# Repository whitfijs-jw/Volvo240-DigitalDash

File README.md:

# DigitalDash

Volvo 240 Digital Dash Project.  Designed to use existing dash connectors (circular connectors w/ 2mm pins, vehicle speed sensor (VSS) connector, and various spade connectors) to
minimize extra wiring effort and installation of superfluous sensors.

## Features
### Plug and play with stock sensors and dash connectors
One of the main goals of the project was to use the existing Volvo 240 connectors. The only additional connectors and wiring needed are for sensors that weren't available on the stock main dash (oil pressure, oil temperature, vacuum/boost pressure, etc). Dash lights (low oil pressure, battery voltage, parking brake,high beams, etc) are functional as well as turn indicators. Fuel level and coolant temperature are functional.
The hardware supports the addition of common accessory sensors such as oil pressure, oil temperature, manifold absolute pressure, and ambient temperature.

### Multiple dash styles
Different Volvo dash styles can be displayed:
#### 240 w/ Tach

#### 240 w/ Clock

#### R-Sport Style

#### P1800 Style

#### 850R

#### 740/940 Style

#### 544/140 Linear Style

#### Early 240 Style

#### 140 Rallye Style

#### 240 Style Custom Layouts

### Accessory Gauges
The raspberry pi 4 supports 2 HDMI outputs so a second screen can be added where normal 52mm accessory gauges would have been placed:

Touch screen controls on this screen can be used to changed between dash layouts and also to reset trip odometers.  The style of the accessory gauges reflects the style of the main dash layout.

## Project Structure:
### /QtDash

This directory contains the hardware and software components that makeup the dash. There are also various visual/graphical assets that are used in the dash app.

#### /QtDash/VolvoDigitalDashModels

This directory contains the Qt app and related unit tests.  It is advised to use [QtCreator](https://www.qt.io/product/development-tools) to edit and compile the app. Using QtCreator to `QtDash/VolvoDigitalDashModels/subdirs.pro` will load both the app and the unit tests. The app is written using C/C++ for interfacing with the various sensors and QML for the UI.

#### /QtDash/Hardware

This directory contains the hardware that has been designed for this project.  Most of the PCBs have been designed using Eagle 7.7 as this is what I am most familiar with. The future of Eagle is questionable as an open source/free tool, so Kicad 6 will be used more and more as I become more familiar with it.

##### /QtDash/Hardware/DashHat

This directory contains the schematics and board files for the PCB that directly interfaces with the Raspberry Pi 40 pin header.  The board is split up into a low voltage (3.3/5V) that is powered from the Pi header and a high voltage (car battery voltage 8-16V) that is powered from the 240 ignition switch via the VSS connector.  The high voltage side is optically isolated from the low voltage side using optoislators.

##### /QtDash/Hardware/Cold Start Power Supply

This directory contains the schematics and board files for the cold start tolerant power supply design based around the LM3488. The input range is ~3V-24V and the output is ~5V rated at 3A.  During bench testing the input power needs to be above 5V when first powering up, and then could drop to ~3V while still continuously powering the Pi. This is a little overkill as the battery voltage during cranking only momentarily drops to 3V-4V before recovering very quickly to >10V.

##### /QtDash/Hardware/Screen Mounting

This directory contains the `.stl` files for mounting the HSD123KPW2-D10 12.3" TFT LCD using the stock 240 dash mounting holes.  These mounts will put the screen flush with the surrounding dash. The mounts and all other 3D modeling/CAD has been done using [Onshape](https://cad.onshape.com/documents/a41976d465f773bfdcbe5a50/w/2aee2fa256d8f08e0c531410/e/f563da56c6a88e94f86205e9). Included in the public OnShape document are models of the main PCB, HSD123KPW2-D10 LCD, screen mounts, etc.

##### /QtDash/Hardware/Simulation

This directory contains SPICE simulations of various circuits used in the dash. This is more of a scratchpad than it is a serious attempt at accurate real-life simulations.

##### /QtDash/Hardware/TachAdapter

This directory contains the schematics and board files for the tach signal adapter.  This board takes the high voltage pulses (>30V on my 88 245) and converts them to a square wave that can be used by the dash software to calculate RPM. The high voltage pulses are optically isolated from the dash/pi side to prevent any unwanted noise or damage to the pi or other hardware.

##### /QtDash/Hardware/VSS Adapter

This directory contains the schematics and board files for the VSS signal adapter. This board is based on the MAX9924 VR signal conditioning IC and takes the VR signal from the stock Volvo differential cover sensor and converts it into a square wave to be used by the dash software to calculated speed.

### /buildroot

This directory contains Buildroot, a tool used to generate a custom embedded Linux system that runs on the Pi. Buildroot allows us to generate a stripped down Linux system that has just enough to get the dash running.  This is the directory where you'll need to be to start linux image builds.

Below are relevant directories for this project within the buildroot directory structure:

#### /buildroot/board/volvodash

This directory contains the rootfs overlay for the dash as well as the custom scripts and configurations used whilst building the dash linux image. 

#### /buildroot/configs

This directory contains the configuration files for various boards. The relevant files for this project are `volvodash_defconfig` and `volvodash_rpi4_defconfig`.

#### /buildroot/output/images

This directory contains the outputs of the buildroot compilation process. After buildroot is done compiling the custom linux image, compiling the specified target packages, and constructing the target rootfs and bootfs, an image that can be flashed on to an SD card is placed here.  `sdcard.img` can then be flashed on to an SD card to be used on a pi.  As a part of the compilation/building the Qt Dash app should be compiled and placed within this image.  For more detailed information see *Setting Up Buildroot* below.

## Project components:
- Raspberry Pi 3 or Raspberry Pi 4/400
- 12.3" bar TFT LCD
- Qt Quick w/ EGLFS project to display renders of gauges
- Buildroot linux to cut down on footprint and boot time
- i2c/spi adc interface for reading temp, fuel, speed, etc sensors
- i2c IO expander for warning lights
- Raspberry Pi daughter board to read various sensors.
- DC/DC power supply for screen, pi and sensor supplies, if necessary
- Cheap USB GPS for speedometer and heading (leaving the original speedo behind the dash? Not planning on implementing a validated odometer)

## Current parts (mainly driven by availability):
- HSD123KPW2-D10 12.3" TFT 1920x720 LCD Display w/ HDMI conversion board and custom mounts
- MCP3208 for ADC inputs
- MCP23017SS for dash warning lights and left/right blinkers
- ILQ1 for isolated I/O inputs (3 for 12 inputs) add one more to completely fill the MCP23017
- IL300 for 12V to 3.3V for isolated analog signals (rheostat and battery voltage)
- lM358D for driving IL300 12V isolated analog inputs
- LMV324 & TVS912D for 5V to 3.3V analog sensor inputs
- VK-162 USB GPS module -- needs to be manually configured with u-blox u-center to get 10Hz update rate.
- (optional and separate) LM3488 switching power supply to maintain 5.1V out from 3V-24V input
- (optional) MAX9924 VSS conditioning circuit
- (separate) optocoupler tach pulse input.

## Accessory Screen Parts (optional)
- Adafruit TFP401 HDMI/DVI Decoder to 40-Pin TTL Breakout - With Touch
- BuyDisplay.com 5" IPS 800x480 LCD Screen TFT w/ touch module ER-TFT050-6-5781-4859
- extended 40-pin flat cable
- USB cable for touch screen interface

## Setting up buildroot

Buildroot will build the custom linux image.  The image being build is based on the raspberry-piX 32-bit images provided from the buildroot project.  Right now there is only support for raspberry pi 3 and pi 4/400.  Things are still a bit of a mess here and depending on your flavor of Linux you might have to setup your system a little differently than others.  You can find a lot of good information here on host packages that are absolutely necessary: [Buildroot System Requirements](https://buildroot.org/downloads/manual/manual.html#requirement)

Detailed instructions for setting up a virtual machine and the build environment are found [here](SetupBuildEnv.md)

## Remote Access

1. SSH (ethernet)

After boot the pi will be configured with a static ip address of 192.168.42.2.
Assuming you're running a version of linux that has network-manager you can run some variation of the following after connecting the pi to your computer with an ethernet cable:

`nmcli con add con-name dash-target type ethernet ifname <your-ethernet-interface> ip4 192.168.42.1/24`

`nmcli con up id dash-target`

You can find your ethernet interface by running:

`ip addr show`

You're looking for something like `enp2s0` or `eth0` depending on your flavor of linux.

After setting everything up you can test the connection using:

`ping 192.168.42.2` 

on the host machine and then run:

`ssh root@192.168.42.2` 

and enter the default credentials

## Dash Configuration

After linux is done booting and loading kernel modules, the init system will automatically start the Qt app stored in the /opt directory.  When the app is initializing it will load two configuration files from the /opt directory:

- config.ini
- config_gauges.ini
- config_odo.ini
- config_can.ini

These files are parsed using QSettings ([more info here](https://doc.qt.io/qt-5/qsettings.html)).

### Sensor input configuration (config.ini)

The sensor configuration file contains the configuration for the analog sensor inputs, dash light inputs, user inputs, tach inputs, vss inputs, the isolated 12V inputs, and backlight PWM control.

#### Sensor channels

Under the **[sensor_channel]** section the following inputs can be configured:

| Parameter | Description |
|---|---|
| *coolant_temp* | Stock Volvo coolant temperature sensor/sender. |
| *fuel_level* | Stock Volvo Fuel Level sender |
| *oil_pressure* | Oil Pressure sender |
| *oil_temp* | Oil temperature sender |
| *map_sensor* | MAP sensor sensor (GM 0-5V) |
| *ambient_temp* | Ambient Temperature sender (any NTC sensor can be used) |
| *dimmer_voltage* | Dimmer Rheostat output voltage |
| *fuse8_12v* | Volvo Fuse 8 to measure battery voltage |
| *reference* | A channel configured to measure the unregulated pi 5V supply to decrease measurment error.  If this is not used it is assumed that the supply is exactly 5V. You can alternatively measure your 5V power rail and provide that in the configurations below.|
| *v_supply* | Optional value to set the exact value of the 5V supply.  If left empty exactly 5.0V will be used |

The default configuration is as follows:
```
[sensor_channels]
coolant_temp=0
fuel_level=1
oil_pressure=2
oil_temp=3
map_sensor=5
ambient_temp=4
dimmer_voltage=6
fuse8_12v=7
reference=-1
v_supply=5.1
```

#### Dash Light Inputs

Under the **[dash_lights]** section the following inputs can be configured:

| Parameter | Description |
|---|---|
| *oil_pressure_sw* | Stock oil pressure switch |
| *od_lamp* | Overdrive lamp |
| *high_beam* | High beam indication |
| *brake_failure* | brake failure indication |
| *bulb_failure* | bulb failure indication |
| *charging* | Alternator D+/Battery charge failure indication |
| *blinker_left* | Left blinker indication |
| *blinker_right* | Right blinker indication |
| *od_lamp_auto* | auto trans OD lamp |
| *check_engine* | Check Engine indication |
| *parking_brake* | Parking Brake engagement indication |
| *conn_32_pin3* | Half moon connector pin 3 (ABS light in newer 240s) |

and one additional option:

- *active_low* -- Optoisolator outputs are open collector so this should be set to 1 unless changes to the hardware have been made

The default configuration is as follows:

```
[dash_lights]
active_low=1
oil_pressure_sw=0
od_lamp=1
high_beam=2
brake_failure=3
bulb_failure=7
charging=6
blinker_left=5
blinker_right=4
od_lamp_auto=8
check_engine=9
parking_brake=10
conn_32_pin3=11
```
#### User Input configuration

There are 4 user inputs in Rev C and greater hardware.  They are active low inputs on the otherwise unused pins on the MCP23017.

Under the **[user_inputs]** section the following inputs can be configured:

| Parameter | Description |
|---|---|
| *input_1* | User input 1 pin number |
| *input_2* | User input 2 pin number |
| *input_3* | User input 3 pin number |
| *input_4* | User input 4 pin number |
| *input_1_map* | User input 1 key mapping |
| *input_2_map* | User input 2 key mapping |
| *input_3_map* | User input 3 key mapping |
| *input_4_map* | User input 4 key mapping |

The default configuration is as follows:

```
[user_inputs]
input_1=12
input_2=13
input_3=14
input_4=15
input_1_map="Key_Left"
input_2_map="Key_A"
input_3_map="Key_B"
input_4_map="Key_Right"
```

Available key mappings are:
```
"Key_Left"
"Key_Right"
"Key_Up"
"Key_Down"
"Key_A"
"Key_B"
"Key_C"
"Key_D"
"Key_1"
"Key_2"
"Key_3"
"Key_4"
```

"Key_Left" and "Key_Right" are used to change dash layouts.  Other keys will be mapped to other functions in the future (resetting trip counters, for example).

#### MAP Sensor configuration

Designed for a GM style 0-5V output MAP sensor (1 bar, 2 bar, 3 bar). Under the **[map_sensor]** section the following parameters can be configured:

| Parameter | Description |
|---|---|
| *p_0v* | pressure when sensor output is 0V |
| *p_5v* | pressure when sensor output is 5V |
| *p_atm* | atmospheric pressure |
| *units* | pressure units used for above values.  "kPa", "psi" or "bar" should be used |

The default configuration is for a 3 bar GM style map sensor:

```
[map_sensor]
p_0v=3.6
p_5v=315
units="kPa"
```

#### Temperature Sensor (NTC) Configuration

An array of NTC sensor configurations. Calibration curves are calculated using the [Steinhart-Hart equation](https://en.wikipedia.org/wiki/Steinhart%E2%80%93Hart_equation). Under the **[temp_sensor]** the following parameters can be configured:

| Parameter | Description |
|---|---|
| *type* | Sensor type.  Options are "coolant", "oil", and "ambient" |
| *r_balance* | Resistance of the balance resistor. This can be calculated based on the high and low resistances expected during operation. |
| *t1_temp* 	|  Temperature at first calibration point |
| *t1_R* 		| Resistance at first calibration point |
| *t2_temp* 	| Temperature at second calibration point |
| *t2_R* 		| Resistance at second calibration point |
| *t3_temp* 	| Temperature at third calibration point |
| *t3_R* 		| Resistance at third valibration point |
| units | Temperature units used.  Options are "C", "K", "F" |

The default configuration is designed for an early type stock 240 coolant temp sensor, a VDO 325-905 Oil temperature sender, and a random ambient temp sensor for a BMW off Amazon.

```
[temp_sensor]
size=3
[temp_sensor/1]
type="coolant"
r_balance=470
t1_temp=60
t1_R=217
t2_temp=90
t2_R=87
t3_temp=100
t3_R=67
units="C"
[temp_sensor/2]
type="oil"
r_balance=150.0
t1_temp=19.5
t1_R=1325
t2_temp=100
t2_R=78.5
t3_temp=157
t3_R=40.5
units="C"
[temp_sensor/3]
type="ambient"
r_balance=6490
t1_temp=1.0
t1_R=15800
t2_temp=20
t2_R=6400
t3_temp=36
t3_R=3360
units="C"
```

#### Resistive Sensor Configuration

An array of resistive sensor configurations. Calibration values can be interpolated (not advised unless a lot of data points are available) or can be fitted with a polynomial of an arbitray order.  Usually a 2nd order polynomial is good enough.  The following parameters can be configured:

| Parameter | Description |
|---|---|
| *type* | Sensor type.  Options are "coolant", "oil", and "ambient" |
| *fit* | Type of fit. Options are "interpolate" or "polynomial, N" with N as the polynomial order.
| *r_balance* | Resistance of the balance resistor. This can be calculated based on the high and low resistances expected during operation. |
| *r* | Calibration resistance values.|
| *y* | Calibration y values |
| *units* | Units of calibration y values |
| *lag* | Lag factor (0-1).  Used to filter values with the difference equation: **y[n] = lag \* x[n] + (1 - lag) \* y[n-1]** Default value is 1.0. |
|*lag_decay*| Lag decay factor.  If set to a non-zero value the following equation will dictate the lag factor value used above: **lagStart=1-*lag*, lag[n] = lagStart \* (1 - *lag_decay*)^(n)** and saturates at the value set by *lag*. Large values will decay quickly, small values slowly.  Default value is 0.0.  |

The default configuration is designed for a VDO 360-028 Oil pressure sender and a 240-33Ohm Volvo 240 Fuel level sender.

```
[resistive_sensor]
size=2
[resistive_sensor/1]
type="oil_pressure"
fit=polynomial,2
r_balance=43.0
r=10.0,48.0,82.0,116.0,184.0
y=0.0,1.0,2.0,3.0,5.0
units="bar"
lag=1.0
[resistive_sensor/2]
type="fuel_level"
fit=polynomial,3
r_balance=91.0
r=240,196,153,125,103,87,67,45,33
y=0.0,12.5,25.0,37.5,50.0,62.5,75.0,87.5,100
units="%"
lag=0.2
```

#### Analog 12V inputs.

To measure signals that are inherently tied to battery voltage there are 2 linearized opto-isolated inputs.  The following parameters can be configured:

| Parameter | Description |
|---|---|
| *name* | Sensor name.  "voltmeter" is the only one currently used |
| *opto_r1* | Isolated side (R59 in schematic below) |
| *opto_r2* | Opto-isolator gain resistor R2 (R62 in schematic below) |
| *input_r1* | High side resistor of voltage divider for input into opto-isolator. (R71 in schematic below) |
| *input_r2* | Low side resistor of voltage divivider for input into opto-isolator. (R72 in schematic below) |
| *k3* | Opto-isolator K3 gain (defined by linearized opto-isolator used and will have to be measured) |
| *offset* | Offset to voltage calculation, the linearized opto-isolator usually has an offset that will need to be accounted for. |
| *x* | Linearized opto-isolator input voltage calibration measurements.  This is the high voltage side.  The more measurement points the better.   |
| *y* | Output voltage calibration measurements.  This is the low voltage side.  Ideally if there was zero offset and a K3 gain of 1.0 these should be x / 10.  This is unlikely to be the case given the binning of the IL300 and LOC11x series. |

##### How to determine K3 value (still need to test on car -- likely to change)
1. In the config.ini file, set *opto_r1*, *opto_r2*, *input_r1*, *input_r2*, and *k3* to 1.0.
2. In the config.ini file, set *offset* to 0.0.
3. Reboot the dash.
4. The output for the voltmeters will now be the real input to the ADC. Usually between 1V-2V for inputs from 8V to 16V.
5. With the car on but not running, measure the voltage at fuse 8.  This will be your first x value.  Take the output of the voltmeter (somewhere between 1V-2V).  This will be your first y value.
6. Start the car and repeat the above step.  These will be your second x and y values.
7. Enter the values determined above in the config.ini file.
8. Reset the *opto_r1*, *opto_r2*, *input_r1*, *input_r2* to their previous values.  You can leave *offset* and *k3* alone.  The software will use your calibration values to calculate the k3 gain and offset.
9. Reboot the dash and verify that the voltages with the car on and running match what you had measured before.

*Note on K3 gain calibration values:*
*Ideally, you would want way more than just 2 points to calibrate with.  If you have access to an adjustable power supply it is recommended to take 5+ measurements from 8V-16V.*

The default configuration is as follows:

```
[12v_analog]
size=2
[12v_analog/1]
name="voltmeter"
opto_r1=490000.0
opto_r2=100000.0
input_r1=100000.0
input_r2=100000.0
k3=1.1536
offset=.087985
x=8.25, 9.05, 9.87, 10.67, 11.52, 12.37, 13.30, 14.15, 14.96, 15.78, 16.78
y=1.05, 1.15, 1.25, 1.35, 1.45, 1.55, 1.65, 1.76, 1.85, 1.95, 2.05
[12v_analog/2]
name="rheostat"
opto_r1=490000.0
opto_r2=100000.0
input_r1=100000.0
input_r2=100000.0
k3=1.1536
offset=.087985
x=8.25, 9.05, 9.87, 10.67, 11.52, 12.37, 13.30, 14.15, 14.96, 15.78, 16.78
y=1.05, 1.15, 1.25, 1.35, 1.45, 1.55, 1.65, 1.76, 1.85, 1.95, 2.05
```

#### Tach Input Configuration

RPM is estimated by measuring the time difference between pulses from the negative terminal of the ignition coil.  The following parameters can be configured:

| Parameter | Description |
|---|---|
| *pulse_per_rot* | Number of tach pulses per rotation (number of cylinders / 2) |
| *max_rpm* | Maximum RPM to resolve.  This should be as low as possible. |
| *avg_num_samples* | Number of samples to average over to estimate RPM |

The default configuration is as follows:

```
[tach_input]
pulse_per_rot=2
max_rpm=9000
avg_num_samples=4
```

#### Vehicle speed sensor input

Designed to used the stock 240 diff cover VSS. The vehicle speed can be estimated using the number of pulses coming from the VSS sensor for every rotation of the rear diff. The following parameters can be configured:

| Parameter | Description |
|---|---|
| *pulse_per_rot* | Number of VSS pulses per rotation (12 for non-ABS and 48 for ABS equipped 240s) |
| *tire_diameter* | Tire diameter (can be used to calculate pulses per unit distance) |
| *diameter_units* | Tire diameter units: "inch", "centimeter", "millimeter", "foot", etc  |
| *pulse_per_unit_distance* | Number of pulses per units distance.   |
| *distance_units* | Distance units for pulses per unit distance:  "mile", "kilometer  |
| *max_speed* | max speed (distance_units / hour).  Keep as low as possible to avoid picking up noise as VSS pulses |

The default configuration is as follows:

```
[vss_input]
pulse_per_rot=12
tire_diameter=24.9
diameter_units="inch"
pulse_per_unit_distance=9720
distance_units="mile"
max_speed="185"
```

#### Backlight control configuration (optional and only somewhat functional)

The stock 240 dimming circuit (Pin 10 on the circular Volvo connector 31) can be used to dim the backlight of the LCD by injecting a PWM signal into the LCD control board. Back light control with the dimmer knob only works when the headlights or running lights are engaged.  Otherwise, the dimmer rheostat does not receive voltage.

The following parameters can be configured:

| Parameter | Description |
|---|---|
| *max_duty_cycle* | Maximimum duty cycle of backlight PWM signal (min_duty_cycle-1.0) |
| *min_duty_cycle* | Minimum duty cycle of backlight PWM signal (0-max_duty_cycle) |
| *lights_off_duty_cycle* | Default duty cycle to use when the headlights or running lights are off |
| *lights_on_duty_cycle* | Default duty cycle to use when headlights or running lights are on|
| *min_dimmer_ratio* | rheostat voltage as a percentage of battery voltage at dimmest setting |
| *max_dimmer_ratio* | rheostat voltage as a percentage of battery voltage at brightest setting |
| *use_dimmer* | flag to use/don't use dimmer |
| *active_low* | PWM signal active low flag |

The default configuration is as follows:

```
[backlight]
max_duty_cycle=1.0
min_duty_cycle=0.05
lights_off_duty_cycle=1.0
lights_on_duty_cycle=0.5
min_dimmer_ratio=0.82
max_dimmer_ratio=0.93
use_dimmer=0
active_low=1
```

### Gauge Configs (config_gauges.ini)
There are a few options in setting up the gauge units and high/low warning indications.  There settings are found within the file config_gauges.ini.  The app will parse this file and will set the various gauge units, min/max values, and high/low warnings.

#### Gauge Config Parameters
| Parameter | Description | Default Value |
|---|---|
|*units*| Gauge Display Units ||
|*low_alarm*| Value below which gauge will indicate a warning ||
|*high_alarm*| Value above which gauge will indicate a warning ||
|*alt_units_enable*| Enable alternate units|*false*|
|*alt_units*|Alternate units|\"\"|
|*alt_units_thres*|Threshold value to switch units|*0.0*|
|*alt_units_above*|If true, use alternate units above threshold.  Otherwise the alternate units are used below the threshold|*false*|

##### Example:
This example sets the units for coolant temperature gauges, in all screens, to celsius.  The gauge will indicate an alarm when the temperature exceeds 100C.
```
[coolant_temp]
units="C"
low_alarm=0.0
high_alarm=100.0
```

#### Available Gauge Units
Below are the available units for each gauge type

| Gauge Type | Available Units |
|---|---|
|**[boost]**|```"bar"``` ```"psi"``` ```"inHg"```|
|**[coolant_temp]**|```"C"``` ```"F"```|
|**[fuel_level]**|```"%"```|
|**[oil_pressure]**|```"bar"``` ```"psi"```|
|**[oil_temperature]**|```"C"``` ```"F"```|
|**[voltmeter]**|```"V"```|
|**[speedo]**|```"mph"``` ```"kph"``` ```"km/h"```|
|**[tacho]**|*none*|

#### Default Gauge Ranges

These are the default gauge ranges for the given units.  These can be assigned to different values in *config_gauges.ini*, but the gauges themselves are prerendered so its not gauranteed that the needle position will align with the displayed value

| Gauge Type | Unit | Min Value | Max Value |
|---|---|---|---|
|**[boost]**| ```"psi"``` | -20 | 30 |
|**[boost]**| ```"bar"```| -1.0| 1.5 |
|**[coolant_temp]**| ```"C"``` | 50 | 120 |
|**[coolant_temp]**| ```"F"```| 120| 250 |
|**[fuel_level]**| ```"%"``` | 0 | 100 |
|**[oil_pressure]**| ```"bar"```| 0| 5 |
|**[oil_pressure]**| ```"psi"``` | 0 | 80 |
|**[oil_temperature]**| ```"C"```| 50| 150 |
|**[oil_temperature]**| ```"F"``` | 120 | 300 |
|**[voltmeter]**| ```"V"```| 10| 16 |
|**[speedo]**| ```"kph"``` ```"km/h"``` | 0 | 220 |
|**[speedo]**| ```"mph"```| 0| 120 |

### Default Values

```
[boost]
units="psi"
low_alarm=-20.0
high_alarm=20.0
[coolant_temp]
units="F"
low_alarm=0.0
high_alarm=200.0
[fuel_level]
units="%"
low_alarm=10.0
high_alarm=200.0
[oil_pressure]
units="bar"
low_alarm=1.0
high_alarm=4.5
[oil_temperature]
units="F"
low_alarm=0.0
high_alarm=220.0
[voltmeter]
units="V"
low_alarm=12.0
high_alarm=15.0
[speedo]
units="mph"
top_value_source="voltmeter"
top_value_units="V"
[tacho]
max_rpm=7000
redline=6000
```

### CAN config (config_can.ini)
Rev C hardware added components to interface with CAN outputs from an aftermarket ECU.  The MCP2515 driver and can0 network interface are loaded when the dash boots and the Dash Qt app attempts to load CAN frame configuration from the *config_can.ini* file.  To date this has only been tested with a Microsquirt on a bench with simulated inputs. If the CAN interface is enabled in the CAN config file, the dash will preferentially use the frame data for a specific gauge over a hardware sensor.

#### Enable/Disable
Under the **[start]** heading in the CAN config file, there is a single option:

| Parameter | Description |
|---|---|
| *use* | true/false to enable/disable the use of incoming CAN data |

#### CAN Frame data
Under the **[can_frame]** heading will come the CAN frame data settings. This is setup based upon information found [here](http://www.msextra.com/doc/pdf/Megasquirt_CAN_Broadcast.pdf).

| Parameter | Description |
|---|---|
| *frame_id* | CAN Frame ID where data is present |
| *offset* | Offset within frame where the data is present |
| *data_size* | Data size in bytes |
| *signed* | true if data is signed |
| *name* | Name of data (map, rpm, tps, etc) -- default values come from the simplified CAN broadcast data from Megasquirt |
| *units* | Units of data |
| *multiply* | Factor to multiply raw value by |
| *divide* | Factor to divide raw value by |
| *add* | Value to add to raw value |
| *gauge* | Gauge to route data to. |

Order of operations is **(raw_data * multiply_factor / divide_factor) + add_value**.  Is this right? No idea.

Example configuration:
```
[start]
use=false
[can_frame]
size=7
[can_frame/1]
frame_id=1512
offset=0
data_size=2
signed=true
name="map"
units="kPa"
multiply=1
divide=10
add=0
gauge="boost"
[can_frame/2]
frame_id=1512
offset=2
data_size=2
signed=false
name="rpm"
units="rpm"
multiply=1
divide=1
add=0
gauge="tacho"
[can_frame/3]
frame_id=1512
offset=4
data_size=2
signed=true
name="clt"
units="F"
multiply=1
divide=10
add=0
gauge="coolant_temp"
[can_frame/4]
frame_id=1512
offset=6
data_size=2
signed=true
name="tps"
units="%"
multiply=1
divide=10
add=0
gauge="none"
[can_frame/5]
frame_id=1513
offset=4
data_size=2
signed=true
name="mat"
units="F"
multiply=1
divide=10
add=0
gauge="none"
[can_frame/6]
frame_id=1515
offset=0
data_size=2
signed=true
name="batt"
units="V"
multiply=1
divide=10
add=0
gauge="voltmeter"
[can_frame/7]
frame_id=1516
offset=0
data_size=2
signed=true
name="vss1"
units="msec^-1"
multiply=1
divide=10
add=0
gauge="none"
```

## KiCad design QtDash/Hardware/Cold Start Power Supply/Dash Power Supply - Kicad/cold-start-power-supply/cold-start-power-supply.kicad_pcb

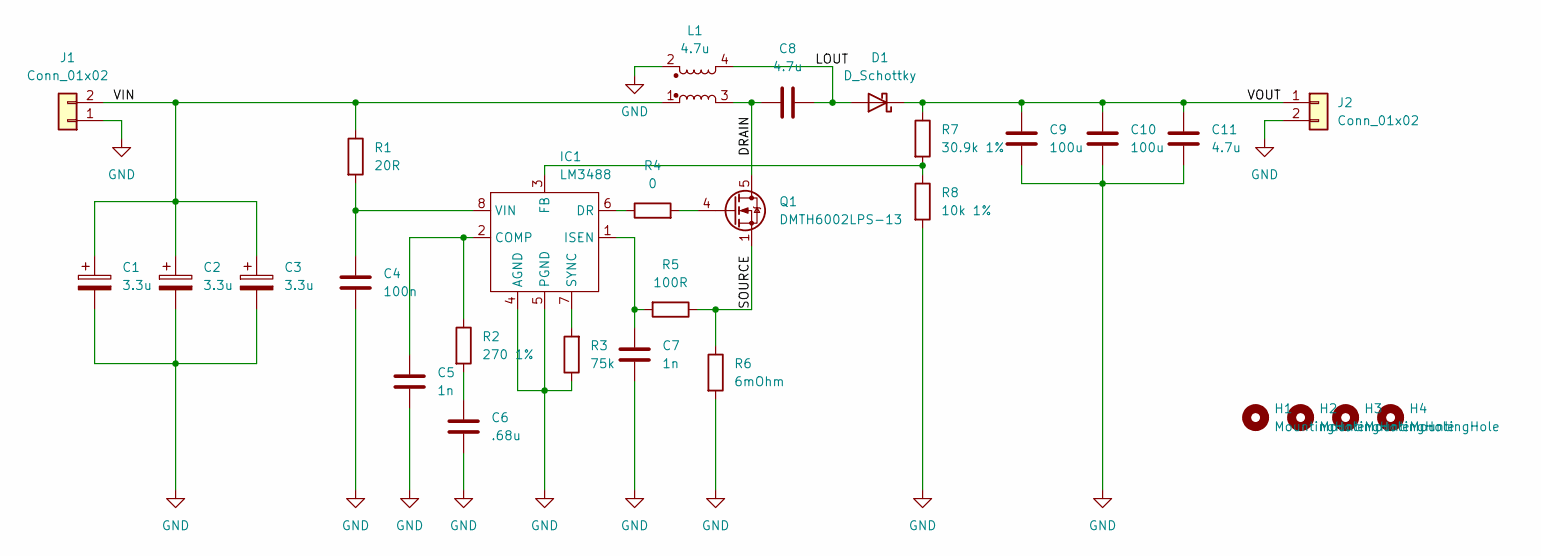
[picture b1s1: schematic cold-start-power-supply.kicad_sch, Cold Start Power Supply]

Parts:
C1, C2, C3: 3.3u; CP_Elec_5x5.3
C4: 100n; C_0603_1608Metric
C5, C7: 1n; C_0603_1608Metric
C6: .68u; C_0603_1608Metric
C8: 4.7u; C_0603_1608Metric
C9, C10: 100u; C_1210_3225Metric
C11: 4.7u; C_1210_3225Metric
D1: D_Schottky; TO-263-2_TabPin1
H1, H2, H3, H4: MountingHole; MountingHole_2.2mm_M2_Pad_Via
IC1: LM3488; MSOP-8_3x3mm_P0.65mm
J1, J2: Conn_01x02; SolderWire-1sqmm_1x02_P5.4mm_D1.4mm_OD2.7mm
L1: 4.7u; DRQ127
Q1: DMTH6002LPS-13; TDSON-8-1
R1: 20R; R_0603_1608Metric
R2: 270 1%; R_0603_1608Metric
R3: 75k; R_0603_1608Metric
R4: 0; R_0603_1608Metric
R5: 100R; R_0603_1608Metric
R6: 6mOhm; R3216
R7: 30.9k 1%; R_1206_3216Metric
R8: 10k 1%; R_0603_1608Metric

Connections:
/DRAIN: C8.2, L1.3, Q1.5 (D)
/LOUT: C8.1, D1.2 (A), L1.4
/SOURCE: Q1.1 (S), Q1.2 (S), Q1.3 (S), R5.1, R6.1
/VIN: C1.1, C2.1, C3.1, J1.2, L1.1, R1.1
/VOUT: C9.1, C10.1, C11.1, D1.1 (K), J2.1, R7.1
GND: C1.2, C2.2, C3.2, C4.2, C5.2, C6.2, C7.2, C9.2, C10.2, C11.2, IC1.4 (AGND), IC1.5 (PGND), J1.1, J2.2, L1.2, R3.1, R6.2, R8.2
unnamed: C4.1, IC1.8 (VIN), R1.2
unnamed: C5.1, IC1.2 (COMP), R2.1
unnamed: C6.1, R2.2
unnamed: C7.1, IC1.1 (ISEN), R5.2
unnamed: IC1.3 (FB), R7.2, R8.1
unnamed: IC1.6 (DR), R4.1
unnamed: IC1.7 (SYNC), R3.2
unnamed: Q1.4 (G), R4.2

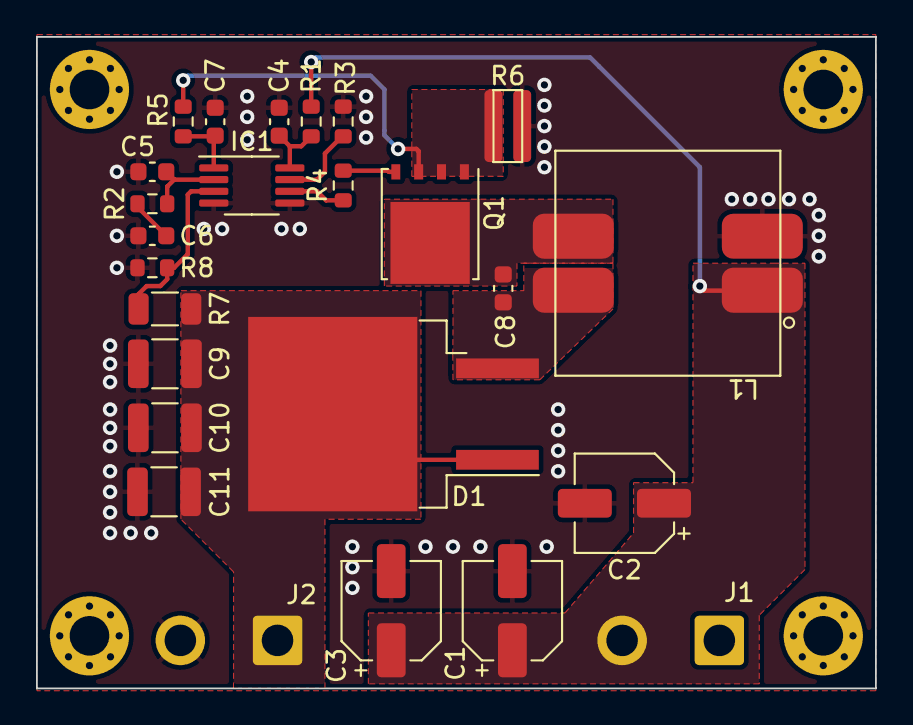
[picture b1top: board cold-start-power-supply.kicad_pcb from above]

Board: 2 copper layers, 46.6 x 36.2 mm, 29 parts (0 on the bottom side), 14 nets.

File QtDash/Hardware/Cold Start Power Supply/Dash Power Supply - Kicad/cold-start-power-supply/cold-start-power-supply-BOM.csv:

"Reference","Value","Qty","DNP","PN"
"C1,C2,C3","3.3u","3","","EEE-FK1K3R3R"
"C4","100n","1","","CL10B104MB8NNNC"
"C5,C7","1n","2","","CL10B102KB8NNWC"
"C6",".68u","1","","CL10B684KO8NFNC"
"C8,C11","4.7u","2","","CL10A475KL8NRNC"
"C9,C10","100u","2","","CL32A107MPVNNNE"
"D1","D_Schottky","1","","STPS8H100G-TR"
"H1,H2,H3,H4","MountingHole","4","",""
"IC1","LM3488","1","","LM3488QMMX/NOPB"
"J1,J2","Conn_01x02","2","",""
"L1","4.7u","1","","DRQ127-4R7-R"
"Q1","DMTH6002LPS-13","1","","DMTH6002LPS-13"
"R1","20R","1","","RC0603JR-0720RL"
"R2","270 1%","1","","RC0603FR-07270RL"
"R3","75k","1","","RC0603JR-0775KL"
"R4","0","1","",""
"R5","100R","1","","RC0603JR-07100RL"
"R6","6mOhm","1","","PRL1632-R006-F-T1"
"R7","30.9k 1%","1","","RC1206FR-0730K9L"
"R8","10k 1%","1","","RC0603FR-1010KL"

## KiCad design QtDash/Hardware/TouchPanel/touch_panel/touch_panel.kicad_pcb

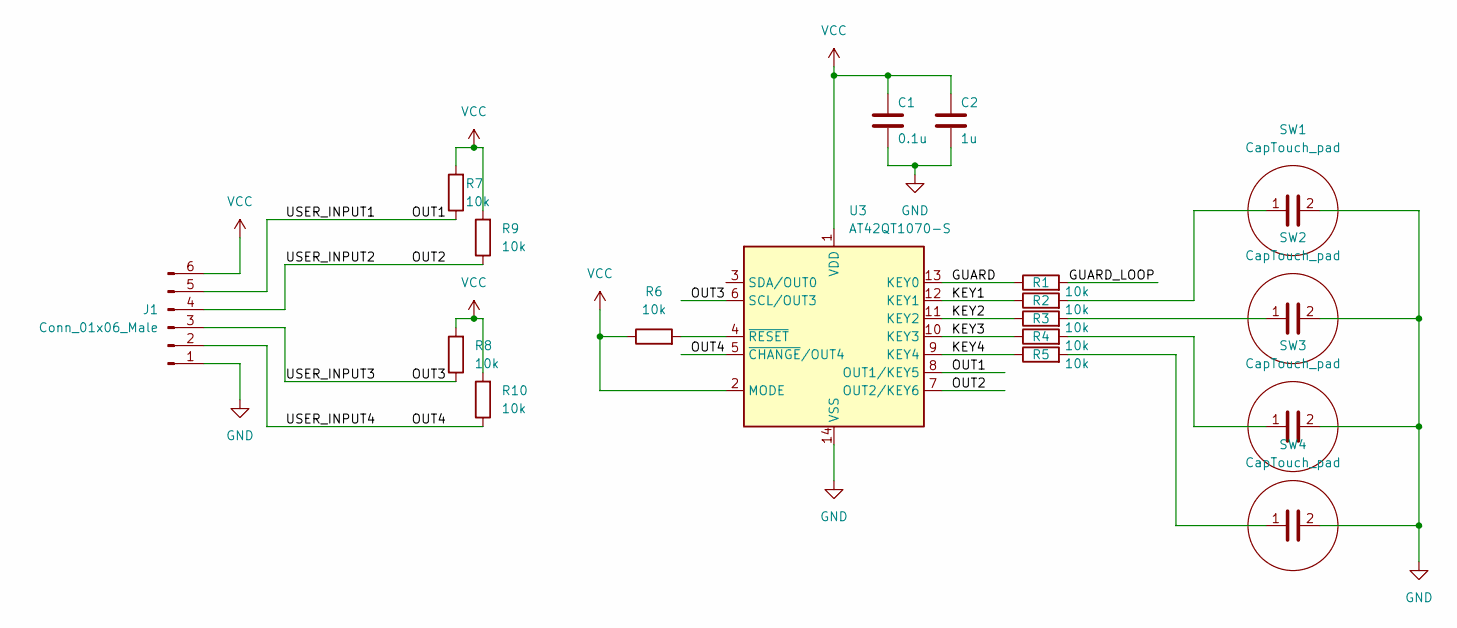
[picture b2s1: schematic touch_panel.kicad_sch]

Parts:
C1: 0.1u; C_0603_1608Metric_Pad1.08x0.95mm_HandSolder
C2: 1u; C_0603_1608Metric_Pad1.08x0.95mm_HandSolder
J1: Conn_01x06_Male; JST_PH_S6B-PH-SM4-TB_1x06-1MP_P2.00mm_Horizontal
R1, R2, R3, R4, R5, R6, R7, R8, R9, R10: 10k; R_0603_1608Metric_Pad0.98x0.95mm_HandSolder
SW1, SW2, SW3, SW4: CapTouch_pad; CAPTOUCH_12.5
U3: AT42QT1070-S; SOIC-14_3.9x8.7mm_P1.27mm

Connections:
/GUARD: R1.1, U3.13 (KEY0)
/GUARD_LOOP: R1.2
/KEY1: R2.1, U3.12 (KEY1)
/KEY2: R3.1, U3.11 (KEY2)
/KEY3: R4.1, U3.10 (KEY3)
/KEY4: R5.1, U3.9 (KEY4)
/OUT1: J1.5, R7.1, U3.8 (OUT1/KEY5)
/OUT2: J1.4, R9.1, U3.7 (OUT2/KEY6)
/OUT3: J1.3, R8.1, U3.6 (SCL/OUT3)
/OUT4: J1.2, R10.1, U3.5 (~CHANGE/OUT4)
GND: C1.2, C2.2, J1.1, SW1.2, SW2.2, SW3.2, SW4.2, U3.14 (VSS)
unnamed: R2.2, SW1.1
unnamed: R3.2, SW2.1
unnamed: R4.2, SW3.1
unnamed: R5.2, SW4.1
unnamed: R6.2, U3.4 (~RESET)
VCC: C1.1, C2.1, J1.6, R6.1, R7.2, R8.2, R9.2, R10.2, U3.1 (VDD), U3.2 (MODE)

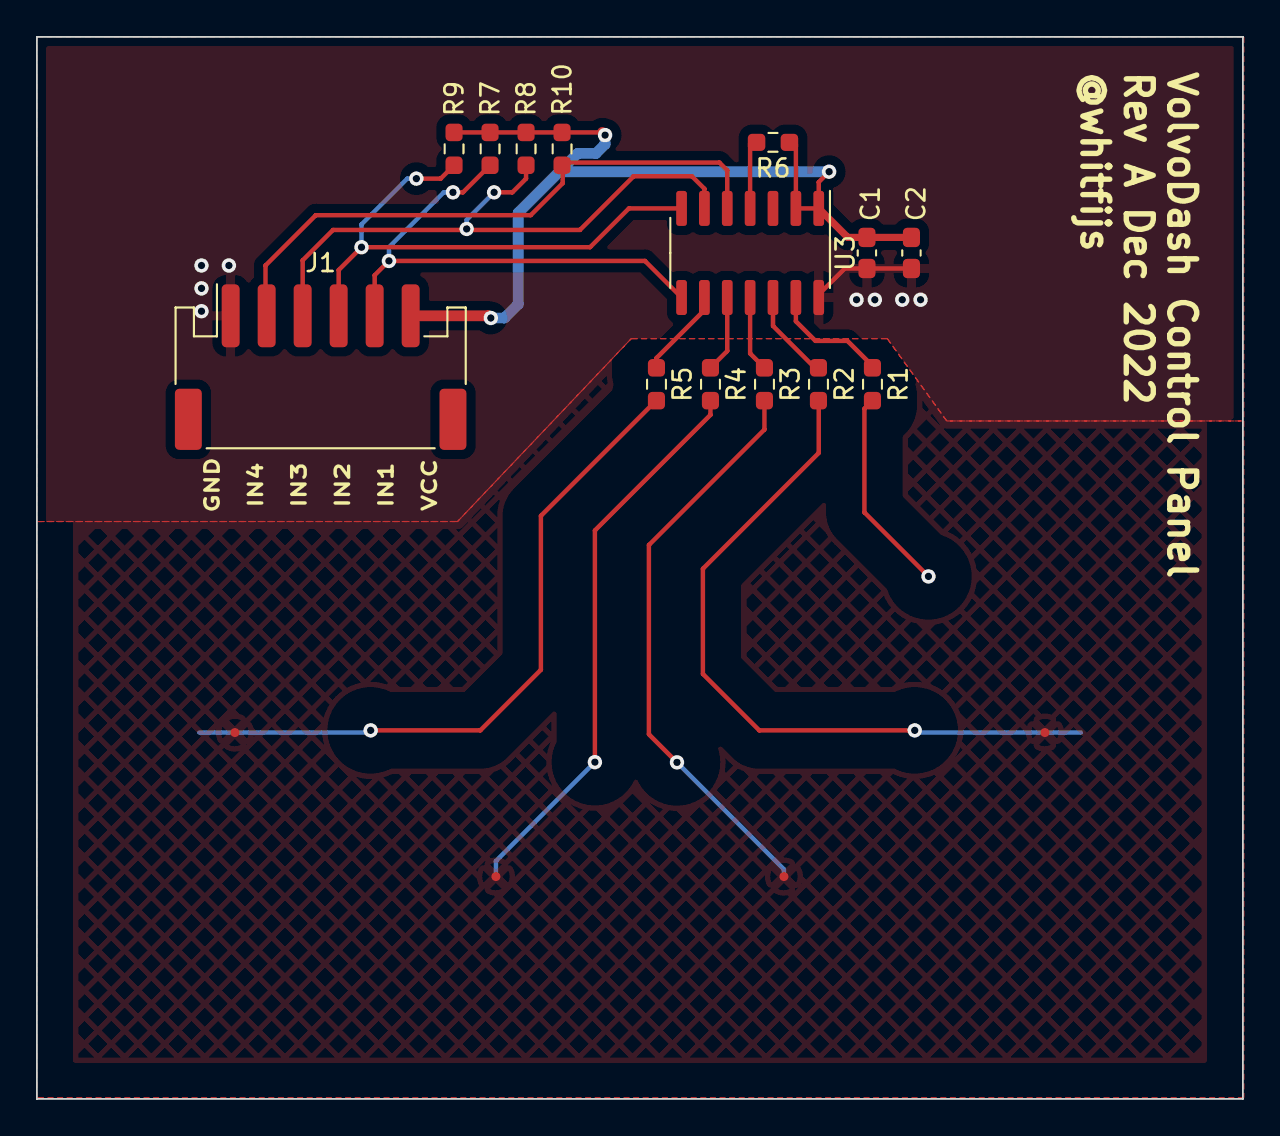
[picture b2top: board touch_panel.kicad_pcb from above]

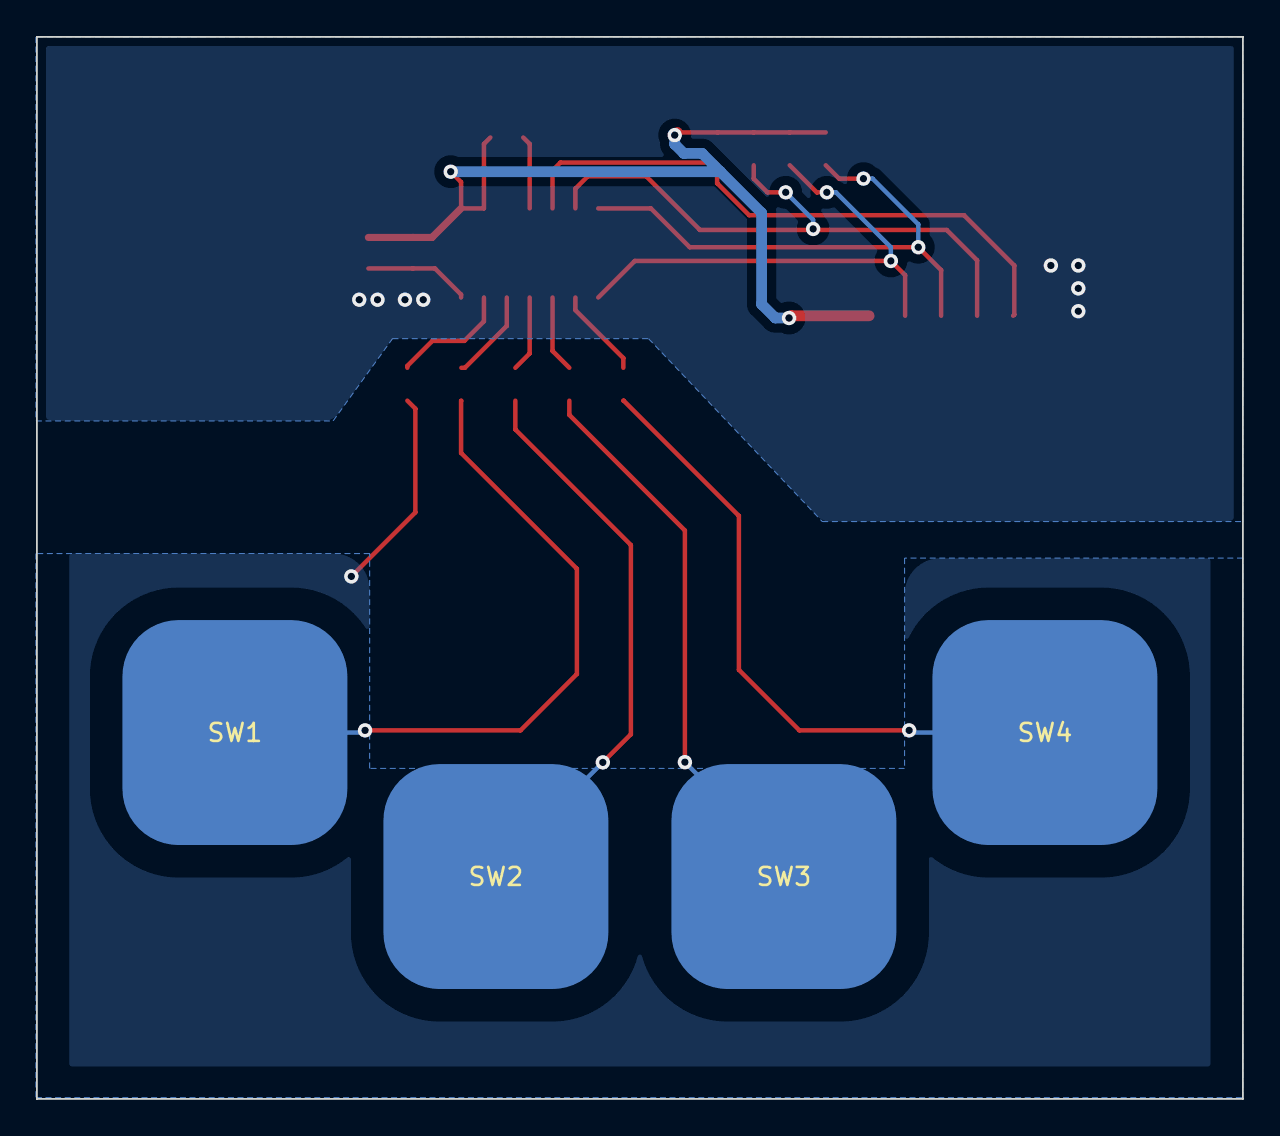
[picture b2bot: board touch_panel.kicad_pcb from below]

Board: 2 copper layers, 67.0 x 59.0 mm, 18 parts (4 on the bottom side), 16 nets.

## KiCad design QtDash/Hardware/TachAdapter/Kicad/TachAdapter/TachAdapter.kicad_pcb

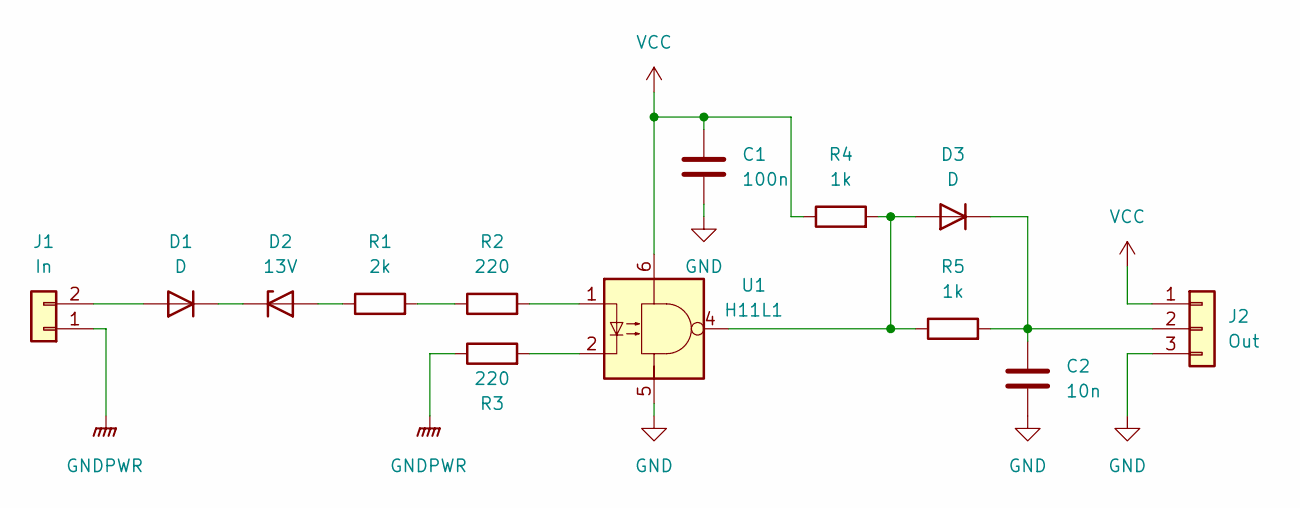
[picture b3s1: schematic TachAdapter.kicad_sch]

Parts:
C1: 100n; C_0603_1608Metric
C2: 10n; C_0603_1608Metric
D1, D3: D; D_SMA
D2: 13V; D_SMB
J1: In; SolderWire-1.5sqmm_1x02_P6mm_D1.7mm_OD3mm
J2: Out; SolderWire-1.5sqmm_1x03_P6mm_D1.7mm_OD3mm
R1: 2k; R_1206_3216Metric
R2, R3: 220; R_1206_3216Metric
R4, R5: 1k; R_0603_1608Metric
U1: H11L1; 6-SMD

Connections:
GND: C1.2, C2.2, J2.3, U1.5
GNDPWR: J1.1, R3.1
unnamed: C2.1, D3.1 (K), J2.2, R5.2
unnamed: D1.1 (K), D2.1 (K)
unnamed: D1.2 (A), J1.2
unnamed: D2.2 (A), R1.1
unnamed: D3.2 (A), R4.2, R5.1, U1.4
unnamed: R1.2, R2.1
unnamed: R2.2, U1.1
unnamed: R3.2, U1.2
VCC: C1.1, J2.1, R4.1, U1.6

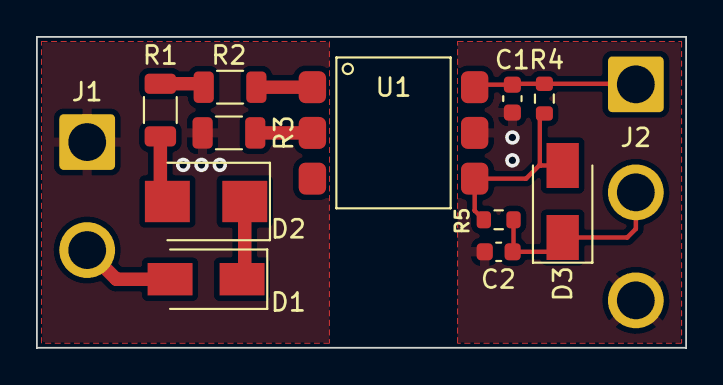
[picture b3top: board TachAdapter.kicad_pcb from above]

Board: 2 copper layers, 36.1 x 17.3 mm, 13 parts (0 on the bottom side), 11 nets.

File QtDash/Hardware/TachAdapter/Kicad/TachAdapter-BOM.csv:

"Reference","Value","Datasheet","Footprint","Qty","DNP","PN"
"C1","100n","https://mm.digikey.com/Volume0/opasdata/d220001/medias/docus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","Capacitor_SMD:C_0603_1608Metric","1","","CL10B104MB8NNNC"
"C2","10n","https://mm.digikey.com/Volume0/opasdata/d220001/medias/docus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","Capacitor_SMD:C_0603_1608Metric","1","","CL10B103KB8NNNC"
"D1","D","https://www.mouser.com/datasheet/2/115/ds15004-3103949.pdf","Diode_SMD:D_SMA","1","","RS2GA-13-F"
"D2","13V","https://www.mouser.com/datasheet/2/80/CZRB5338B_HF_Thru17590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","Diode_SMD:D_SMB","1",""," CZRB5350B-HF"
"D3","D","~","Diode_SMD:D_SMA","1","DNP","RS2GA-13-F"
"J1","In","~","Connector_Wire:SolderWire-1.5sqmm_1x02_P6mm_D1.7mm_OD3mm","1","",""
"J2","Out","~","Connector_Wire:SolderWire-1.5sqmm_1x03_P6mm_D1.7mm_OD3mm","1","",""
"R1","2k","https://www.vishay.com/doc?20043","Resistor_SMD:R_1206_3216Metric","1","","CRCW12062K00JNEAHP"
"R2,R3","220","~","Resistor_SMD:R_1206_3216Metric","2","","CRCW1206220RFKEAHP"
"R4,R5","1k","https://www.yageo.com/upload/media/product/products/datashee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","Resistor_SMD:R_0603_1608Metric","2","","RC0603JR-071KL"
"U1","H11L1","https://www.onsemi.com/pub/Collateral/H11L3M-D.PDF","volvodash:6-SMD","1","","H11L1"

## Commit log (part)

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2022-01-21 - moved dash lights over to fast timer -- indicators might not respond to fast blinkers - droped medium timer to 150msec update
2022-01-23 topic/new-gauge-designs: - added clockwise/counterclockwise flag to gauge - 850 coolant gauge set to clockwise false so it works? Non lo so.
2022-01-25 bugfix/hardware-revA-issues: - added 0.5mm clearance to screen through holes
2022-01-26 bugfix/hardware-revA-issues: - first draft of mount
2022-01-27 bugfix/hardware-revA-issues: - added outputs solder points for fuse 16 and fuse 8 power - added 12V input solder points switched power? - added some ground vias on for 5V ground return path -- things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
2022-01-28 bugfix/hardware-revA-issues: - added squashfs rootfs to sd card image -- should be able to switch between ext4 and squash using cmdline.txt
2022-02-01 bugfix/hardware-revA-issues: - output of IL300s were oscillating under load -- added 100n capacitor (bodged on revA) - 12V inputs are only 0-3.3V signals -- K3 used to compensate for different for now
2022-02-03 bugfix/hardware-revA-issues: - fixed issues with clock seconds hand going the long way around when crossing from 59 to 0
2022-02-06 - copied revA version of pi adapter into /QtDash/Hardware/DashHat/Board Revisions/Rev A - generated gerbers and schematic pdf -- will need to modify the schematic to reflect what was actually built -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
2022-02-06 - update Board Revisions/Rev A schematic with final assembly values notes on final assembly
2022-02-10 topic/new-gauge-designs: - added shroud things on coolant and temp gauges in rsport cluster - updated fonts in rsport cluster svg
2022-02-11 topic/new-gauge-designs: - messing around with gauge borders - changed r-sport gauge needle color
2022-02-12 bugfix/hardware-revA-issues: - added supply only board for testing separately and more cheaply - added resistor values to cold start board library
2022-02-16 topic/switch-to-64-bit: - buildroot adjusted to work without rpi-userland packages - vc4 and v3d compiled into kernel - qml manually rotated 180 degrees - additional QT_QPA parameters added to init.d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
2022-02-17 bugfix/tach-adapter-updates: - added kicad project for tach adapter -- testing out kicad
2022-02-18 topic/new-gauge-designs: - updated bounds of 850r boost gauge
2022-02-19 topic/sensor-and-gauge-value-conditioning: - re-arranged dash initialization to avoid flippy text during boot
2022-02-20 topic/sensor-and-gauge-value-conditioning: - adjusted K3 value for 12V analog inputs, still not quite right -- consider using polynomial fits - adjusted decimal point values for gauges
2022-02-25 topic/component_optimization: - fixed issue with vss source signal/slot hookup - vss input now working -- tested with function generator
2022-03-01 topic/component-optimization: - 20k resistor on vin of power supply should have been 20R - fixed silk screen on cold start power supply - re-arranged components a via for cleaner return paths
2022-03-01 topic/component-optimization: - added some more output capacitors
2022-03-02 topic/more-accurate-gauge-needles: - tested on pi -- looks good - adjusted widths and colors in 740/940 layout
2022-03-03 topic/tach-adapter-udpates: - added kicad and eagle relevant gitignore fields
2022-03-05 - Filled in documentation for sensor configuration file (config.ini)
2022-03-06 bugfix/gauge-configs-dont-propagate: - ugly solution to convert internal sensor units to display units from config_gauges.ini
2022-03-08 - fixed spacing in README.md
2022-03-14 bugfix/analog-12v-input-linearity-issues: - added datasheets for IL300 alternatives - added .lib file for IL300
2022-03-26 topic/hardware-revb-support: - fixed text scaling for warning light
2022-03-30 topic/hardware-revb-support: - added writing of odometer value to pi dash - added Q_OBJECT to sensor_odometer to be able to use its writeOdometerValue signal
2022-04-06 topic/rpi4-support: - non-working configs
2022-04-12 topic/backlight-pwm-control: - added 50% backlight output on boot before app takes over (inittab) - changed cmdline.txt to boot from ext4 partition
2022-04-15 topic/rpi4-support: - moved preview image to top
2022-04-23 topic/backlight-pwm-control: - added (weak) pullup on PWM input to PWM adapter board - probably just need to make a backlight driver on the main board
2022-04-28 topic/hardware-revc: - replaced larger molex connector smaller molex connector
2022-04-29 topic/hardware-revc: - small layout changes to the main board
2022-05-04 topic/hardware-revc: - replaced dd with fbv in /sbin/preinit - tested pwm.h changes
2022-05-12 topic/hardware-revc: - added libsocketcan to target packages - added can-utils (to be removed later) - added Qt SerialBus package - added can0 interface bring up in etc/network
2022-05-13 topic/hardware-revc: - added beginngings of QCanBusDevice initialization
2022-05-20 topic/hardware-revc: - added parts list for rev c
2022-06-02 topic/hardware-revc: - gerbers generated for rev c - pcb's ordered from JLC pcb - rev c board preview images generated
2022-07-08 bugfix/hardware-revc-fixes: - added proper CAN support to rpi4 image -- working with MCP2515 on rev C hardware - fixed missing i2cdev package in rpi4 linux image -- mcp23017 working - MCP3208 moved t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
2022-10-03 bugfix/hardware-revc-fixes: - filled in more config unit tests -- temp sensor configs
2022-10-06 bugfix/hardware-revc-fixes: - changed 4-pin user input to 6-pin molex nano-fit connector to accomodate 3.3V and GND
2022-12-28 bugfix/hardware-revc-fixes: - added start out touch panel for 4 user inputs - fixed issues with host dash setup - changed changing of screen to key released and ignore duplicate events
2023-01-16 bugfix/hardware-revc-fixes: - user inputs pins are configurable - user input key mapping is somewhat configurable (Key_Left,Key_Right are needed to changed screens) - updated DashLights to accept gen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
2023-02-07 bugfix/hardware-revc-fixes: - initial value of resistive sensor previousValue was undefined
2023-02-16 feature/long-press-mapping-for-user-inputs-trip-odometer-resetting: - initial go at long press mapped to resetting trip counters - TODO: make long press mapping configurable
2023-03-14 feature-45: - key press on accessory screen cycles main screen (not configurable or very portable)
2023-03-15 feature-45: - added necessary changes to eglfs_hdmi.json and rcS enviroment variables setup to make touch display with with evdev
2023-03-16 feature-45: - added 740/940 style gauges to accessory screen layout -- side screen switches to 740/940 style gauges for 740 and 850 layouts - added 740 style oil temperature gauge
2023-03-16 feature-45: - added p1800 style boost/vaccum gauge and p1800 style clock assets -- no qml element yet
2023-03-18 feature-45: - added r-sport style accessory gauges
2023-04-06 feature/46-pi-zero-support: - added pi0w image configs -- uses rpi4 linux defconfig - image builds but needs to be tested
2023-11-28 50-map-sensor-atmospheric-offset-not-configurable: - updated readme for new options
2023-12-05 50-map-sensor-atmospheric-offset-not-configurable: - updated README to reflect changes in the config for the supply voltage
2023-12-05 topic/update-readme: - started updating readme with features - added more screenshots of dash styles
2023-12-07 topic/update-readme: - formatting changes
2023-12-08 topic/S60R-gauges: - added needle center image to Gauge.qml - added S60R style needle center, looks bad
2023-12-09 topic/S60R-gauges: - fixed voltmeter asset
2023-12-22 topic/documentation-update: - added tach adapter revision documentation for kicad and eagle
2023-12-22 topic/documentation-cleanup: - added 3d models for thickened main screen mounts - added accessory screen mount 3d models
2024-02-18 topic/early-240-cluster: - first draft of early 240 gauges
2024-02-20 topic/early-240-cluster: - started adding warning lights to early 240 layout
2024-02-21 topic/early-240-cluster: - added font for 240 style gauge - small update to gauge creator
2024-02-22 topic/early-240-cluster: - updated later 240-style with updated renders
2024-02-23 topic/early-240-cluster: - added accessory gauges to later 240 style svg
2024-02-24 topic/early-240-cluster: - attempted to get things sorted out on early 240 cluster
2024-02-26 topic/early-240-cluster: - updated README
2024-02-27 topic/early-240-cluster: - added border to early 240 cluster
2024-02-27 topic/early-240-cluster: - some changes to how the speedo model max and units get set
2024-03-03 topic/delegate-restructuring: - started add kph alternatives to speedometers
2024-03-03 topic/delegate-restructuring: - cleaned up resources that were not being used
2024-03-04 topic/delegate-restructuring: - fixed some gauge ranges in the rsport layout
2024-03-05 topic/delegate-restructuring: - fixed p1800 center gauge scaling
2024-03-10 55-adc-voltage-calculation-incorrect: - fixed issue with voltmeter calculation after testing in car
2024-03-11 topic/accessory-gauge-units: - updated 740/940 style oil temp gauge to include C units
2024-03-11 topic/accessory-gauge-units: - added support for "km/h" to be used as well as "kph"
2024-03-12 topic/accessory-gauge-units: - fixed integer truncating in gauge min/max values - added default values for given units to simplify config_gauges.ini
2024-03-13 topic/accessory-gauge-units: - updated README to include gauge configs
2024-03-14 topic/accessory-gauge-units: - fixed min/max angle on rsport coolant temp gauge - added clockwise option to gauge creator
2024-03-26 topic/accessory-gauge-units: - removed all traces of 140 rallye specific accessory gauges
2024-04-04 topic/config-cleanup: - cleaned up config class
2024-04-04 topic/config-cleanup: - event timer cleanup
2024-04-06 topic/config-cleanup: - ntc class cleanup
2024-04-07 topic/config-cleanup: - gps source cleanup
2024-04-10 topic/config-cleanup: - cleaned up sensor utils
2024-04-15 topic/gear-indicator: - starts on test for the gear indicator sensor
2024-06-18 topic/config-cleanup: - added more sanity checks to guage classes
2024-12-22 feature/63: - finally fixed absolute paths in dash host app
2024-12-27 bugfix/r-sport-cluster-boost-gauge-units: - made alternatives for r-sport cluster accessory boost gauge that don't have units
2025-02-01 task/cleanup-dash-class: - changed raw pointers to unique_ptr
2025-02-01 tasks/cleanup-dash-class: - made can sensors a vector of unique_ptr and touched... everything - getting can sensors now returns const pointer from unique_ptr, seems to be ok as it should have probabl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
2025-02-02 feature/72: - added screen rotation config option to config.ini - screen can be rotated to any arbirary angle (0 and 180 would be the obvious choices, but I won't screen shame) - frame buffer is not 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
2025-02-03 feature/70: - finalized build environment setup
2025-02-03 task/ll-cleanup: - LL adc driver cleanup
2025-02-04 task/ll-cleanup: - const cleanup
2025-02-04 task/gauge-sensor-cleanup: - lots of const ref and const function cleanup
2025-02-07 topic/config-sonarqube-cleanup: - fixed const and raw for loop
2025-02-09 topic/misc-cleanup: - make_unique updates
2025-03-08 topic/REV-D-hardware: - first draft of ADC driver for stm32u545 - todo: I2c peripheral implementation
2025-04-15 82-bom-missing: - added one more DNP to tach adapter board
2025-11-18 topic/S60R-gauges: - fixed S60R style boost gauge min/max
2025-11-20 topic/gear-indicator: - prototyping discrete bayes filter for estimating current gear - script for generating (poorly) simulated gear and rpm data
2025-11-25 topic/gear-indicator: - intermediate commit -- filling in gear predictor class
2025-12-05 topic/gear-indicator: - started filling in simple sanity check unit tests for GearPredictiveFilter
